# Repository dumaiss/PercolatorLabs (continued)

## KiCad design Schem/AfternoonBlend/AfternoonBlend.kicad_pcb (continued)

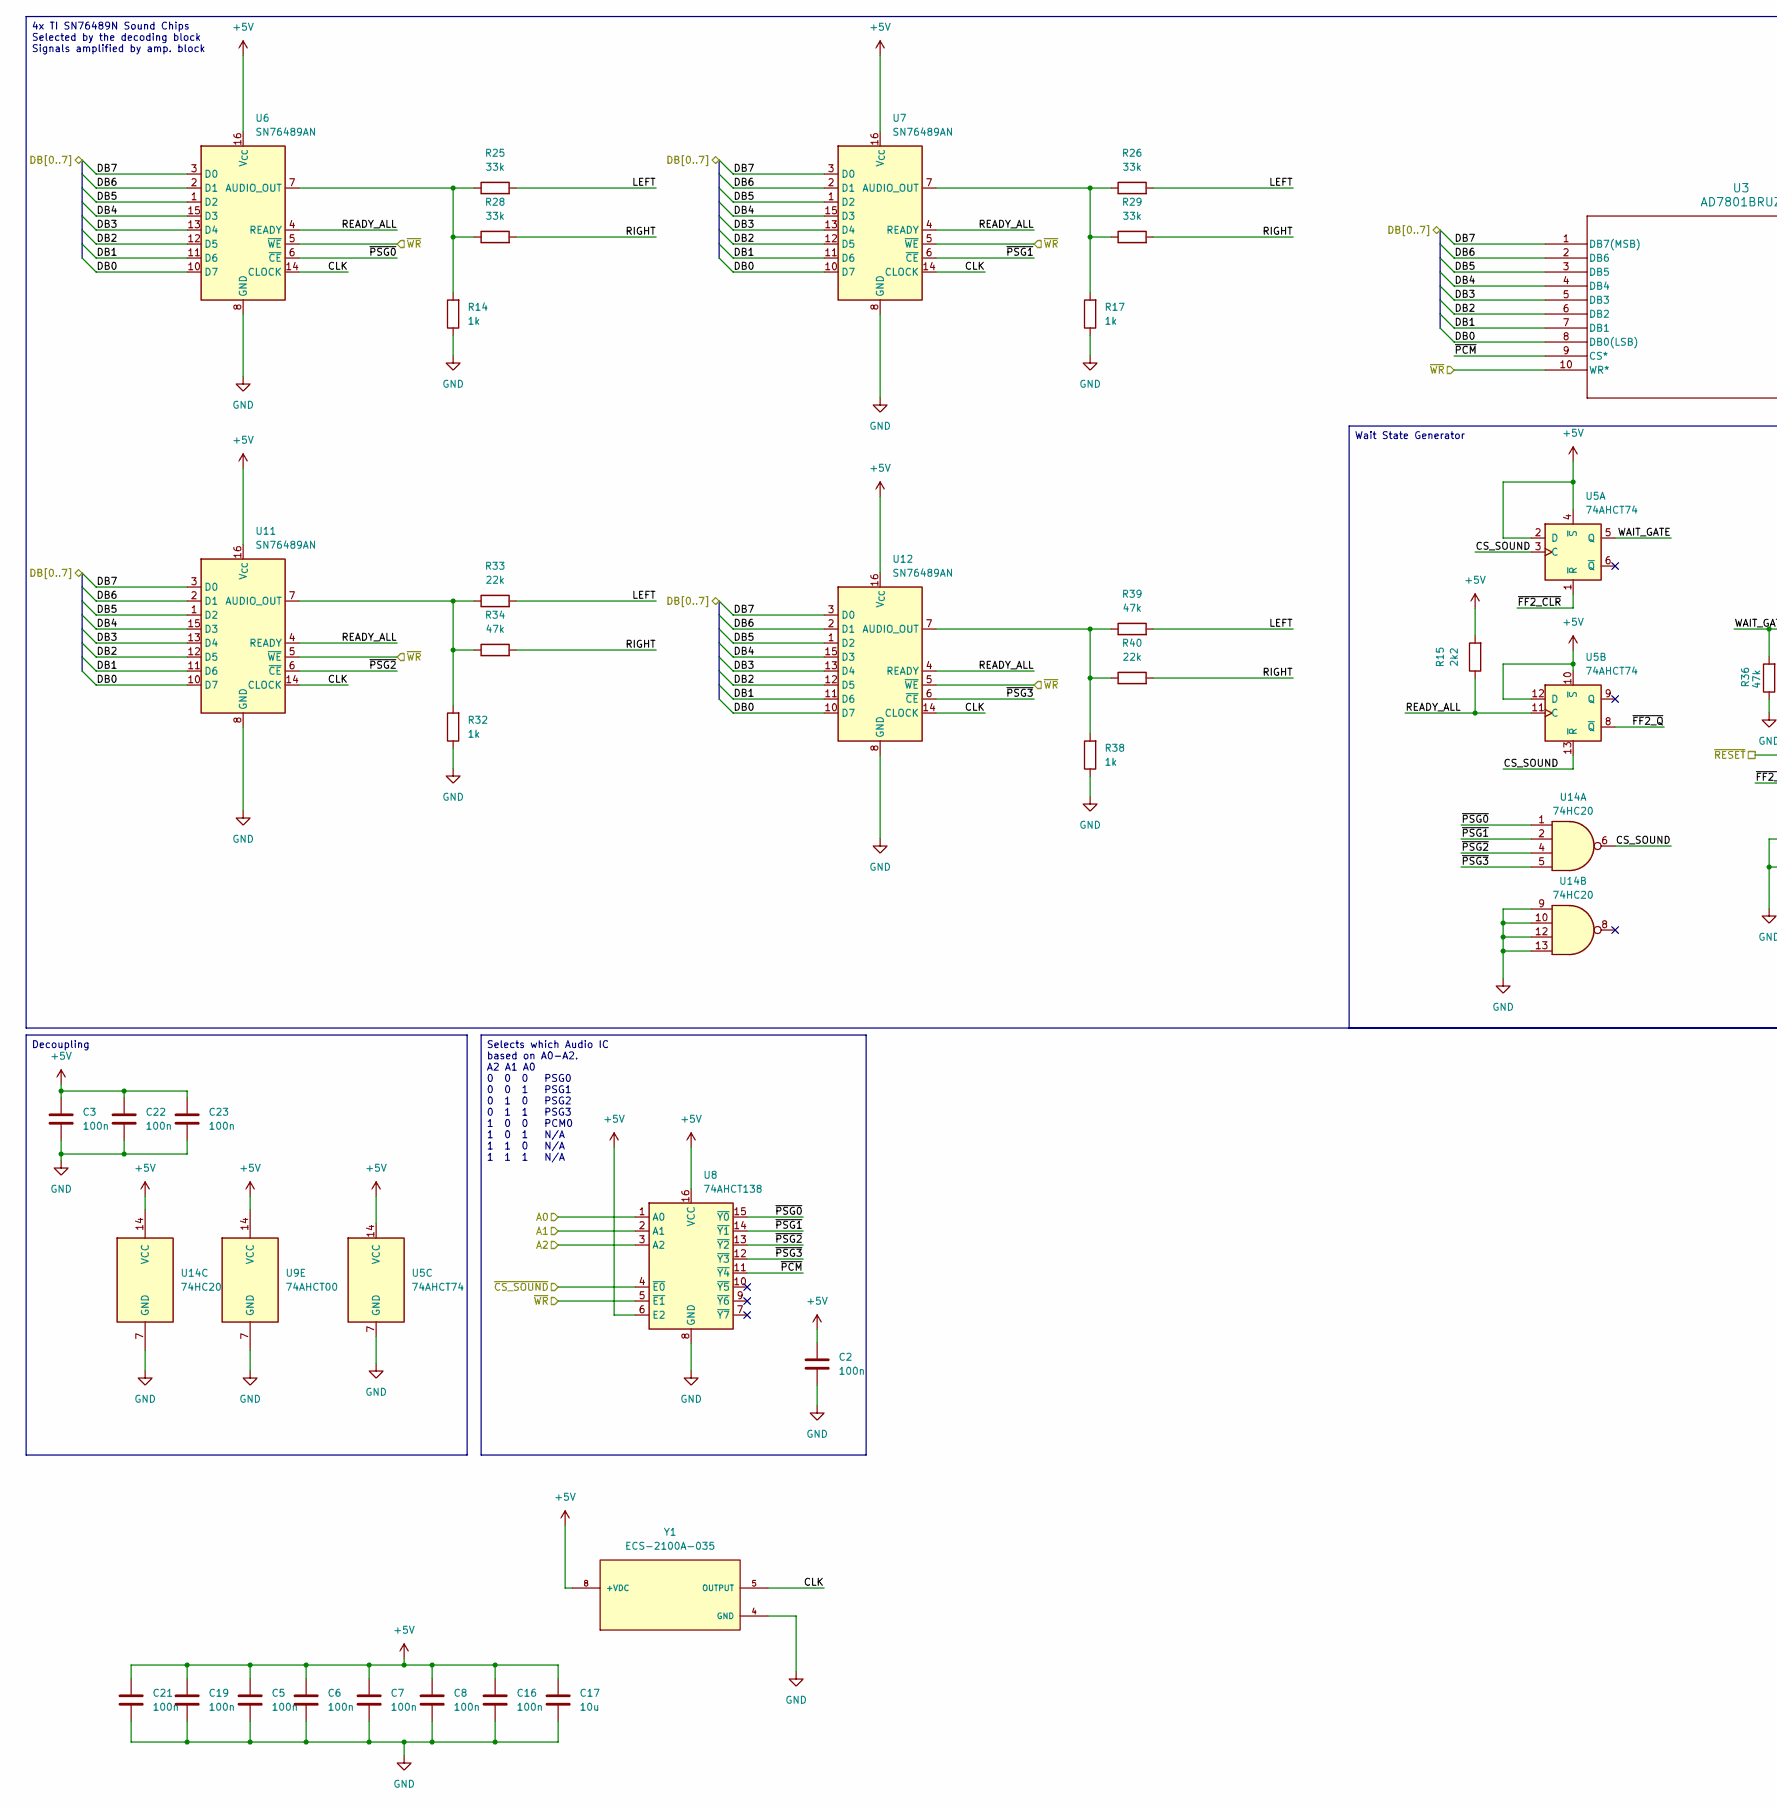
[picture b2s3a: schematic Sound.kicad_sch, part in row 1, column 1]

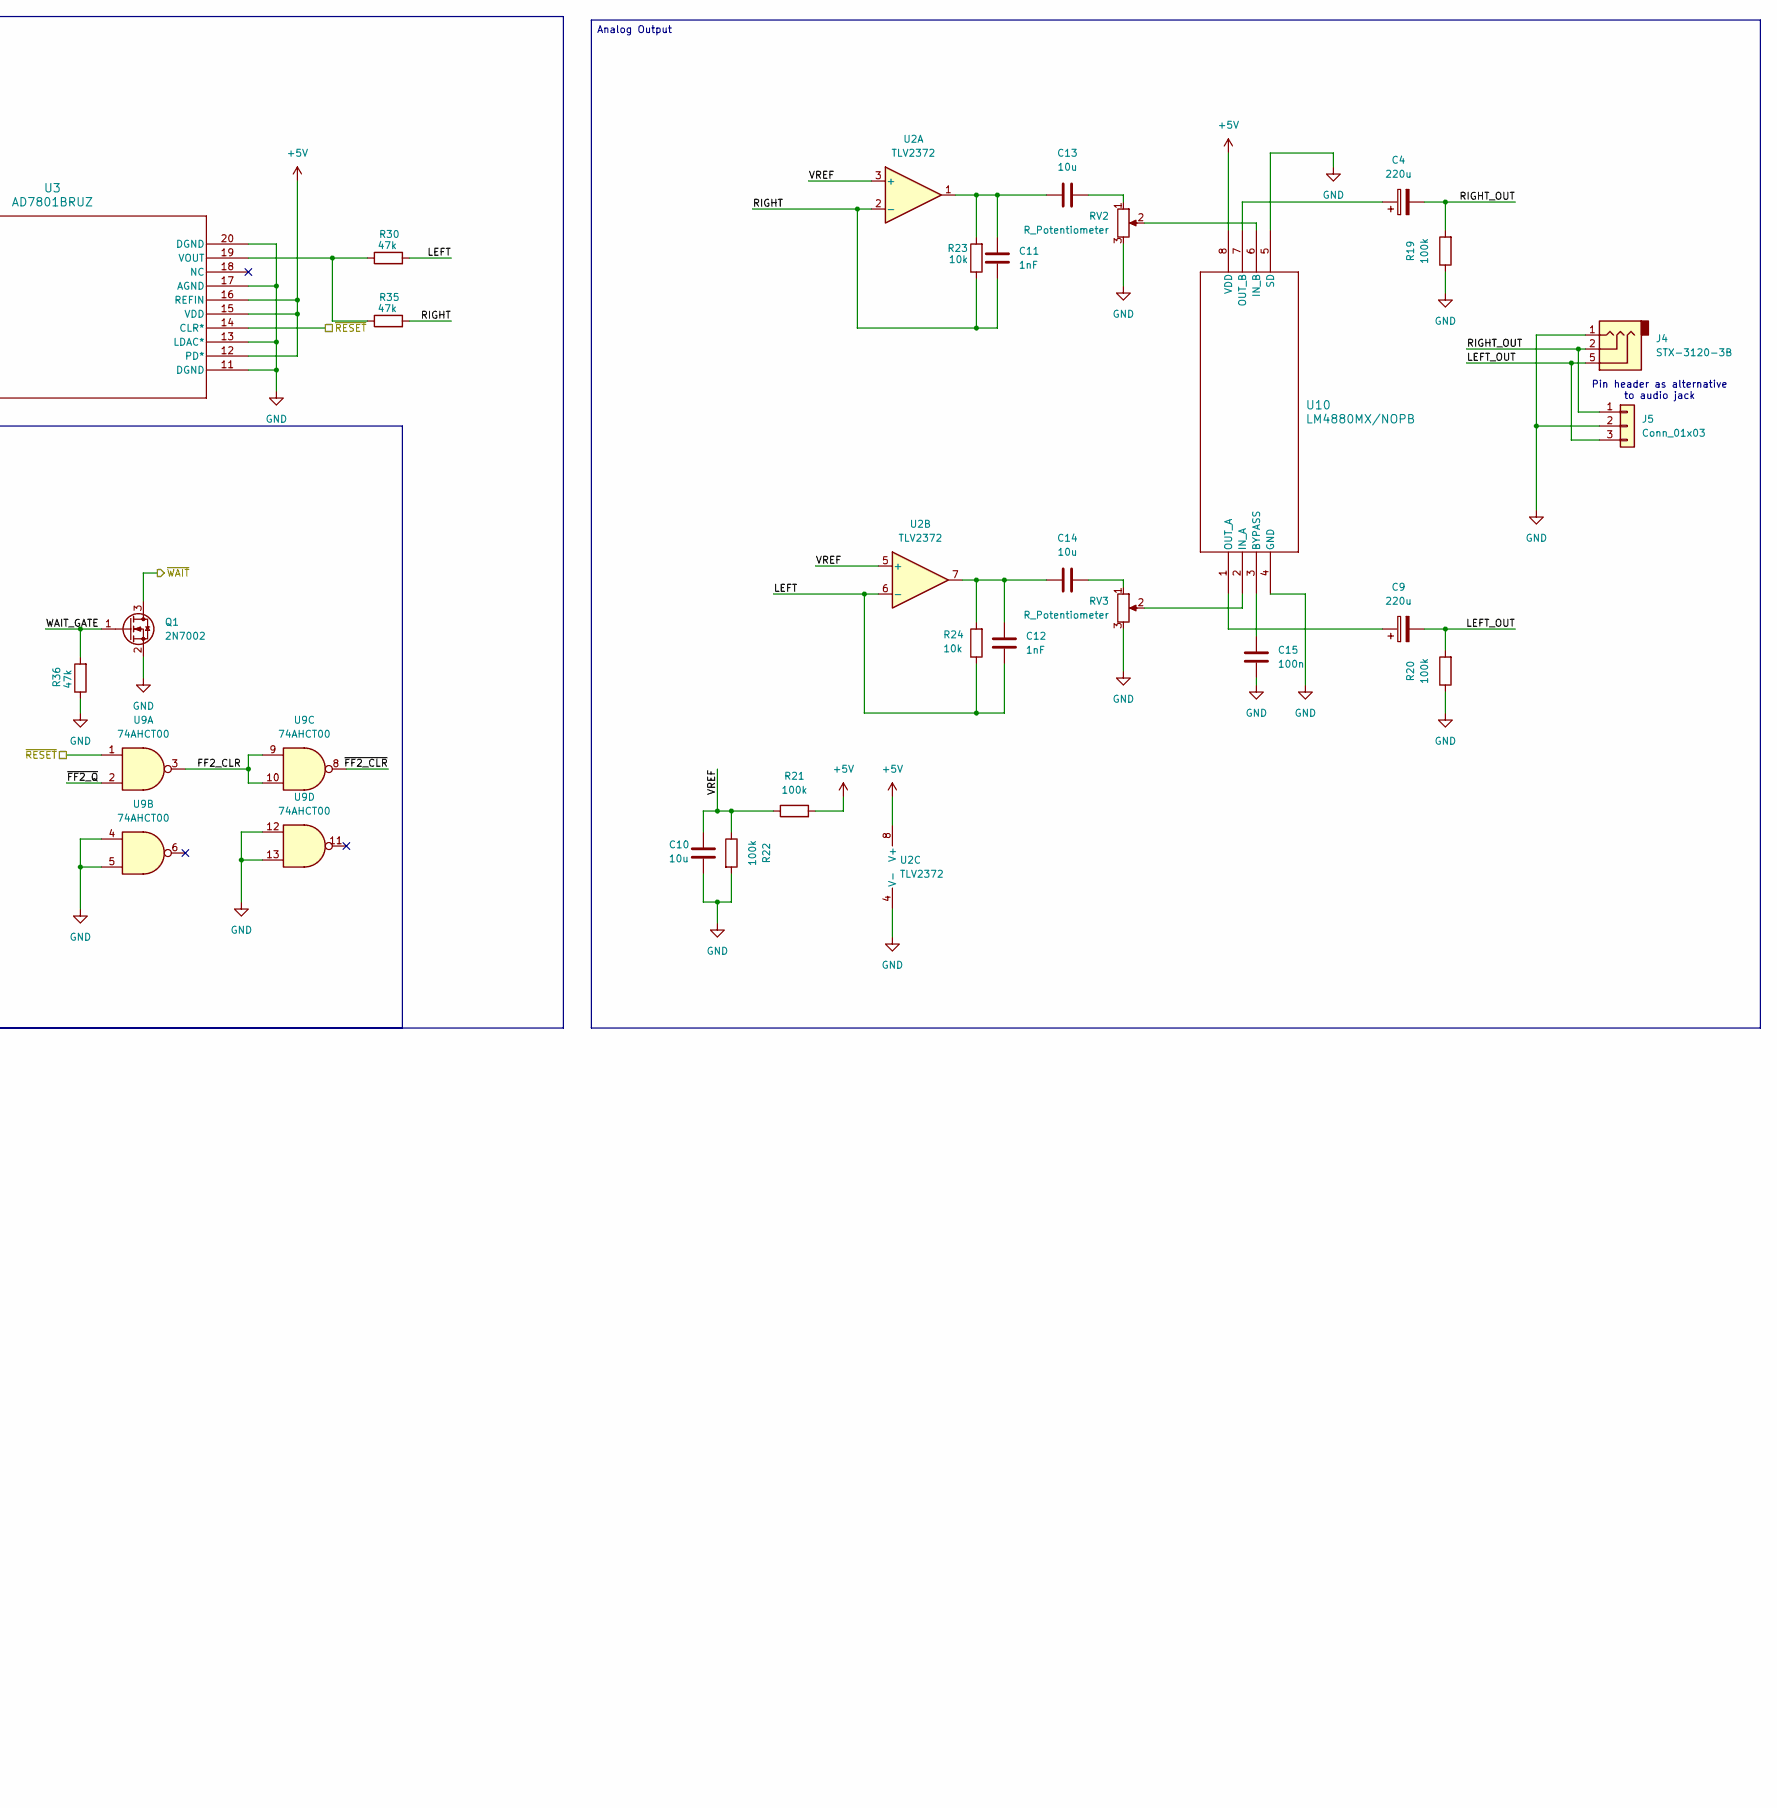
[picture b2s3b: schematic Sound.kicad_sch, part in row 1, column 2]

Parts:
C2, C3, C5, C6, C7, C8, C15, C16, C19, C21, C22, C23: 100n; C_0603_1608Metric; MANUFACTURER_PART_NUMBER C0603C104K5RACTU
C4, C9: 220u; CP_Radial_D6.3mm_P2.50mm; MANUFACTURER_PART_NUMBER 16ZLH220MEFCT16.3X11
C10, C13, C14, C17: 10u; C_0603_1608Metric; MANUFACTURER_PART_NUMBER CL10X106MO8NRNC
C11, C12: 1nF; C_0603_1608Metric; MANUFACTURER_PART_NUMBER C0603C102J5GACTU
J4: STX-3120-3B; KYCON_STX-3120-3B; MANUFACTURER_PART_NUMBER STX-3120-3B
J5: Conn_01x03; PinHeader_1x03_P2.54mm_Vertical; MANUFACTURER_PART_NUMBER 732-5301-ND
Q1: 2N7002; SOT-23; MANUFACTURER_PART_NUMBER BSS138
R14, R17, R32, R38: 1k; R_0603_1608Metric; MANUFACTURER_PART_NUMBER RMCF0603FT1K00
R15: 2k2; R_0603_1608Metric; MANUFACTURER_PART_NUMBER RC0603FR-072K2L
R19, R20, R21, R22: 100k; R_0603_1608Metric; MANUFACTURER_PART_NUMBER RC0603FR-07100KL
R23, R24: 10k; R_0603_1608Metric; MANUFACTURER_PART_NUMBER RC0603FR-0710KL
R25, R26, R28, R29: 33k; R_0603_1608Metric; MANUFACTURER_PART_NUMBER RC0603FR-0733KL
R30, R34, R35, R36, R39: 47k; R_0603_1608Metric; MANUFACTURER_PART_NUMBER RC0603FR-0747KL
R33, R40: 22k; R_0603_1608Metric; MANUFACTURER_PART_NUMBER RC0603FR-0722KL
RV2, RV3: R_Potentiometer; Potentiometer_Bourns_3266W_Vertical; MANUFACTURER_PART_NUMBER 3266W-1-103LF
U2: TLV2372; SOIC-8_3.9x4.9mm_P1.27mm; MANUFACTURER_PART_NUMBER TLV2372IDR
U3: AD7801BRUZ; RU_20_ADI; MANUFACTURER_PART_NUMBER AD7801BRUZ
U5: 74AHCT74; TSSOP-14_4.4x5mm_P0.65mm; MANUFACTURER_PART_NUMBER 74AHCT74PW,118
U6, U7, U11, U12: SN76489AN; DIP-16_W7.62mm_Socket; MANUFACTURER_PART_NUMBER 1-2199298-4
U8: 74AHCT138; SOIC-16_3.9x9.9mm_P1.27mm; MANUFACTURER_PART_NUMBER SN74AHCT138PWR
U9: 74AHCT00; TSSOP-14_4.4x5mm_P0.65mm; MANUFACTURER_PART_NUMBER 74AHCT00PW,118
U10: LM4880MX/NOPB; M08A_TEX; MANUFACTURER_PART_NUMBER LM4880MX/NOPB
U14: 74HC20; TSSOP-14_4.4x5mm_P0.65mm; MANUFACTURER_PART_NUMBER MC74HC20ADTR2G
Y1: ECS-2100A-035; OSC_ECS-2100AX-147.4; PARTREV N/A

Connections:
+5V: C2.1, C3.1, C5.1, C6.1, C7.1, C8.1, C16.1, C17.1, C19.1, C21.1, C22.1, C23.1, R15.2, R21.2, U2.8 (V+), U3.12 (PD*), U3.15 (VDD), U3.16 (REFIN), U5.2 (D), U5.4 (~S), U5.10 (~S), U5.12 (D), U5.14 (VCC), U6.16 (V_{CC}), U7.16 (V_{CC}), U8.6 (E2), U8.16 (VCC), U9.14 (VCC), U10.8 (VDD), U11.16 (V_{CC}), U12.16 (V_{CC}), U14.14 (VCC), Y1.8 (+VDC); also elsewhere on the board
/Device Select Decode/~CS_SOUND: U8.4 (~E0); also elsewhere on the board
/Sound/A0: U8.1 (A0); also elsewhere on the board
/Sound/A1: U8.2 (A1); also elsewhere on the board
/Sound/A2: U8.3 (A2); also elsewhere on the board
/Sound/CLK: U6.14 (CLOCK), U7.14 (CLOCK), U11.14 (CLOCK), U12.14 (CLOCK), Y1.5 (OUTPUT)
/Sound/CS_SOUND: U5.3 (C), U5.13 (~R), U14.6
/Sound/DB0: U3.8 (DB0(LSB)), U6.10 (D7), U7.10 (D7), U11.10 (D7), U12.10 (D7); also elsewhere on the board
/Sound/DB1: U3.7 (DB1), U6.11 (D6), U7.11 (D6), U11.11 (D6), U12.11 (D6); also elsewhere on the board
/Sound/DB2: U3.6 (DB2), U6.12 (D5), U7.12 (D5), U11.12 (D5), U12.12 (D5); also elsewhere on the board
/Sound/DB3: U3.5 (DB3), U6.13 (D4), U7.13 (D4), U11.13 (D4), U12.13 (D4); also elsewhere on the board
/Sound/DB4: U3.4 (DB4), U6.15 (D3), U7.15 (D3), U11.15 (D3), U12.15 (D3); also elsewhere on the board
/Sound/DB5: U3.3 (DB5), U6.1 (D2), U7.1 (D2), U11.1 (D2), U12.1 (D2); also elsewhere on the board
/Sound/DB6: U3.2 (DB6), U6.2 (D1), U7.2 (D1), U11.2 (D1), U12.2 (D1); also elsewhere on the board
/Sound/DB7: U3.1 (DB7(MSB)), U6.3 (D0), U7.3 (D0), U11.3 (D0), U12.3 (D0); also elsewhere on the board
/Sound/FF2_CLR: U9.3, U9.9, U9.10
/Sound/LEFT: C12.1, R24.1, R25.2, R26.2, R30.2, R33.2, R39.2, U2.6 (-)
/Sound/LEFT_OUT: C9.2, J4.5, J5.3, R20.2
/Sound/READY_ALL: R15.1, U5.11 (C), U6.4 (READY), U7.4 (READY), U11.4 (READY), U12.4 (READY)
/Sound/RIGHT: C11.1, R23.1, R28.2, R29.2, R34.2, R35.2, R40.2, U2.2 (-)
/Sound/RIGHT_OUT: C4.2, J4.2, J5.1, R19.2
/Sound/VREF: C10.2, R21.1, R22.1, U2.3 (+), U2.5 (+)
/Sound/WAIT_GATE: Q1.1 (G), R36.2, U5.5 (Q)
/Sound/~FF2_CLR: U5.1 (~R), U9.8
/Sound/~FF2_Q: U5.8 (~Q), U9.2
/Sound/~PCM: U3.9 (CS*), U8.11 (~Y4)
/Sound/~PSG0: U6.6 (~CE), U8.15 (~Y0), U14.1
/Sound/~PSG1: U7.6 (~CE), U8.14 (~Y1), U14.2
/Sound/~PSG2: U8.13 (~Y2), U11.6 (~CE), U14.4
/Sound/~PSG3: U8.12 (~Y3), U12.6 (~CE), U14.5
/Sound/~RESET: U3.14 (CLR*), U9.1; also elsewhere on the board
/Sound/~WAIT: Q1.3 (D); also elsewhere on the board
/Sound/~WR: U3.10 (WR*), U6.5 (~WE), U7.5 (~WE), U8.5 (~E1), U11.5 (~WE), U12.5 (~WE); also elsewhere on the board
GND: C2.2, C3.2, C5.2, C6.2, C7.2, C8.2, C10.1, C15.1, C16.2, C17.2, C19.2, C21.2, C22.2, C23.2, J4.1, J5.2, Q1.2 (S), R14.1, R17.1, R19.1, R20.1, R22.2, R32.1, R36.1, R38.1, RV2.3, RV3.3, U2.4 (V-), U3.11 (DGND), U3.13 (LDAC*), U3.17 (AGND), U3.20 (DGND), U5.7 (GND), U6.8 (GND), U7.8 (GND), U8.8 (GND), U9.4, U9.5, U9.7 (GND), U9.12, U9.13, U10.4 (GND), U10.5 (SD), U11.8 (GND), U12.8 (GND), U14.7 (GND), U14.9, U14.10, U14.12, U14.13, Y1.4 (GND); also elsewhere on the board
unnamed: C11.2, C13.1, R23.2, U2.1
unnamed: C12.2, C14.1, R24.2, U2.7
unnamed: C13.2, RV2.1
unnamed: C14.2, RV3.1
unnamed: R30.1, R35.1, U3.19 (VOUT)
unnamed: R14.2, R25.1, R28.1, U6.7 (AUDIO_OUT)
unnamed: R17.2, R26.1, R29.1, U7.7 (AUDIO_OUT)
unnamed: C15.2, U10.3 (BYPASS)
unnamed: RV3.2, U10.2 (IN_A)
unnamed: RV2.2, U10.6 (IN_B)
unnamed: C9.1, U10.1 (OUT_A)
unnamed: C4.1, U10.7 (OUT_B)
unnamed: R32.2, R33.1, R34.1, U11.7 (AUDIO_OUT)
unnamed: R38.2, R39.1, R40.1, U12.7 (AUDIO_OUT)

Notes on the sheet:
Pin header as alternative to audio jack
Wait State Generator
Decoupling
Analog Output
Selects which Audio IC based on A0-A2. A2 A1 A0 0 0 0 PSG0 0 0 1 PSG1 0 1 0 PSG2 0 1 1 PSG3 1 0 0 PCM0 1 0 1 N/A 1 1 0 N/A 1 1 1 N/A
4x TI SN76489N Sound Chips Selected by the decoding block Signals amplified by amp. block

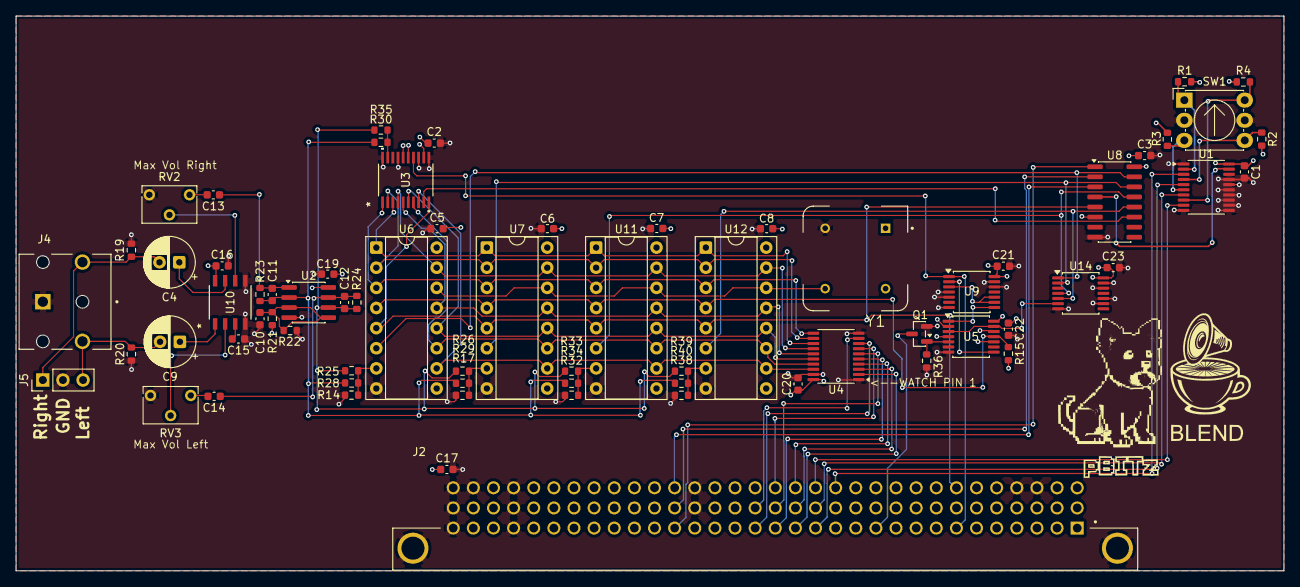
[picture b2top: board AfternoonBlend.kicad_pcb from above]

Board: 4 copper layers, 160.0 x 70.0 mm, 69 parts (0 on the bottom side), 64 nets.

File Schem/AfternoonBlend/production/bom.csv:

Designator,Footprint,Quantity,Value,LCSC Part #
"C1, C15, C16, C19, C2, C20, C21, C22, C23, C3, C5, C6, C7, C8",0603,14,100n,
"C10, C13, C14, C17",0603,4,10u,
"C11, C12",0603,2,1nF,
"C4, C9",CP_Radial_D6.3mm_P2.50mm,2,220u,
J2,AMPHENOL_86093967113T55F1LF,1,~,
J4,KYCON_STX-3120-3B,1,STX-3120-3B,
J5,PinHeader_1x03_P2.54mm_Vertical,1,Conn_01x03,
Q1,SOT-23,1,2N7002,
"R1, R2, R3, R4",0603,4,4k7,
"R14, R17, R32, R38",0603,4,1k,
R15,0603,1,2k2,
"R19, R20, R21, R22",0603,4,100k,
"R23, R24",0603,2,10k,
"R25, R26, R28, R29",0603,4,33k,
"R30, R34, R35, R36, R39",0603,5,47k,
"R33, R40",0603,2,22k,
"RV2, RV3",Potentiometer_Bourns_3266W_Vertical,2,R_Potentiometer,
SW1,Nidec_Copal_SH-7010C,1,SW_Coded_SH-7070,
U1,TSSOP-20_4.4x6.5mm_P0.65mm,1,74HC688,
U10,M08A_TEX,1,LM4880MX/NOPB,
"U11, U12, U6, U7",DIP-16_W7.62mm_Socket,4,SN76489AN,
U14,TSSOP-14_4.4x5mm_P0.65mm,1,74HC20,
U2,SOIC-8_3.9x4.9mm_P1.27mm,1,TLV2372,
U3,RU_20_ADI,1,AD7801BRUZ,
U4,TSSOP-20_4.4x6.5mm_P0.65mm,1,74HCT541,
U5,TSSOP-14_4.4x5mm_P0.65mm,1,74AHCT74,
U8,SOIC-16_3.9x9.9mm_P1.27mm,1,74AHCT138,
U9,TSSOP-14_4.4x5mm_P0.65mm,1,74AHCT00,
Y1,OSC_ECS-2100AX-147.4,1,ECS-2100A-035,

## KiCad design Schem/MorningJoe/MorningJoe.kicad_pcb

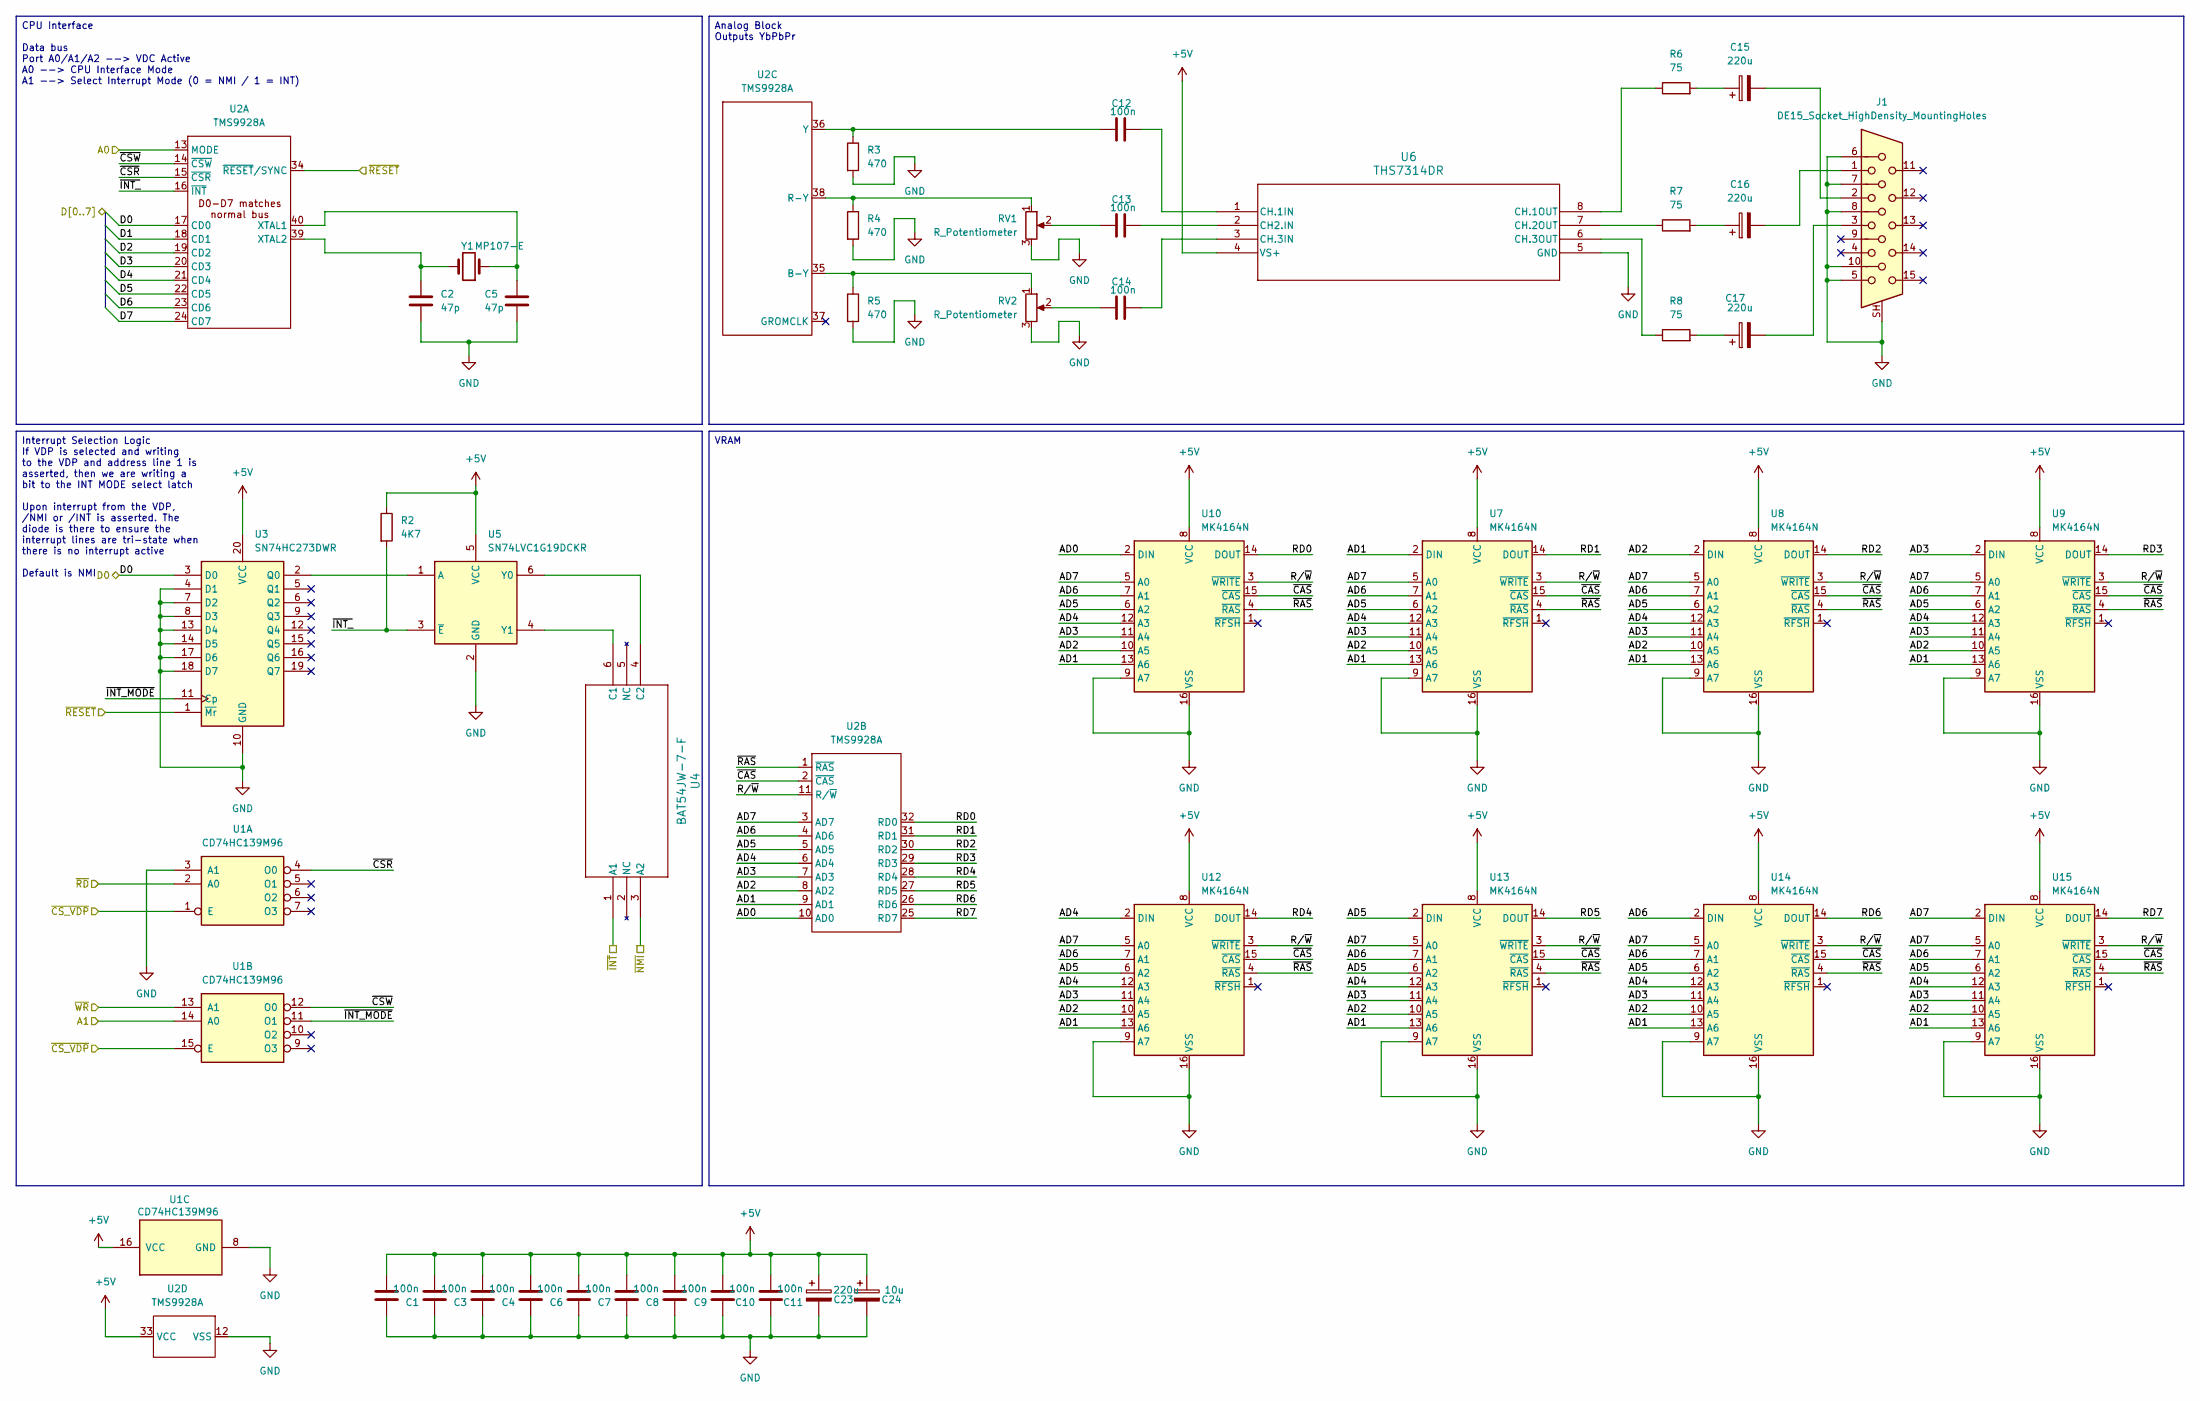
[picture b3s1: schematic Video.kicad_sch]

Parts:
C1, C3, C4, C6, C7, C8, C9, C10, C11, C12, C13, C14: 100n; C_0603_1608Metric; MANUFACTURER_PART_NUMBER C0603C104K5RACTU
C2, C5: 47p; C_0603_1608Metric; MANUFACTURER_PART_NUMBER 885012006021
C15, C16, C17, C23: 220u; CP_Radial_D6.3mm_P2.50mm; MANUFACTURER_PART_NUMBER 16ZLH220MEFCT16.3X11
C24: 10u; CP_Radial_D5.0mm_P2.00mm; MANUFACTURER_PART_NUMBER EEA-GA1E100H
J1: DE15_Socket_HighDensity_MountingHoles; DSUB-15-HD_Socket_Horizontal_P2.29x2.54mm_EdgePinOffset8.35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; MANUFACTURER_PART_NUMBER L77HDE15SD1CH4FVGA
R2: 4K7; R_0603_1608Metric; MANUFACTURER_PART_NUMBER CRCW06034K70FKEA
R3, R4, R5: 470; R_0603_1608Metric; MANUFACTURER_PART_NUMBER RC0603JR-07470RL
R6, R7, R8: 75; R_0603_1608Metric; MANUFACTURER_PART_NUMBER RC0603FR-0775RL
RV1, RV2: R_Potentiometer; Potentiometer_Bourns_3266W_Vertical; MANUFACTURER_PART_NUMBER 3266W-1-103LF
U1: CD74HC139M96; SOIC-16_3.9x9.9mm_P1.27mm; MANUFACTURER_PART_NUMBER CD74HC139M96
U2: TMS9928A; DIP-40_W15.24mm_Socket; MANUFACTURER_PART_NUMBER A 40-LC-TT
U3: SN74HC273DWR; SOIC-20W_7.5x12.8mm_P1.27mm; MANUFACTURER_PART_NUMBER SN74HC273DWR
U4: BAT54JW-7-F; SOT-363_SC-70-6; MANUFACTURER_PART_NUMBER BAT54JW-7-F
U5: SN74LVC1G19DCKR; SOT-363_SC-70-6; MANUFACTURER_PART_NUMBER SN74LVC1G19DCKR
U6: THS7314DR; D8; MANUFACTURER_PART_NUMBER THS7314DR
U7, U8, U9, U10, U12, U13, U14, U15: MK4164N; DIP-16_W7.62mm_Socket; MANUFACTURER_PART_NUMBER 1-2199298-4
Y1: MP107-E; Crystal_HC49-U_Vertical; MANUFACTURER_PART_NUMBER MP107-E

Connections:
+5V: C1.1, C3.1, C4.1, C6.1, C7.1, C8.1, C9.1, C10.1, C11.1, C23.1, C24.1, R2.1, U1.16 (VCC), U2.33 (VCC), U3.20 (VCC), U5.5 (VCC), U6.4 (VS+), U7.8 (VCC), U8.8 (VCC), U9.8 (VCC), U10.8 (VCC), U12.8 (VCC), U13.8 (VCC), U14.8 (VCC), U15.8 (VCC); also elsewhere on the board
/Device Select Decode/~CS_VDP: U1.1 (E), U1.15 (E); also elsewhere on the board
/Video/A0: U2.13 (MODE); also elsewhere on the board
/Video/A1: U1.14 (A0); also elsewhere on the board
/Video/AD0: U2.10 (AD0), U10.2 (DIN)
/Video/AD1: U2.9 (AD1), U7.2 (DIN), U7.13 (A6), U8.13 (A6), U9.13 (A6), U10.13 (A6), U12.13 (A6), U13.13 (A6), U14.13 (A6), U15.13 (A6)
/Video/AD2: U2.8 (AD2), U7.10 (A5), U8.2 (DIN), U8.10 (A5), U9.10 (A5), U10.10 (A5), U12.10 (A5), U13.10 (A5), U14.10 (A5), U15.10 (A5)
/Video/AD3: U2.7 (AD3), U7.11 (A4), U8.11 (A4), U9.2 (DIN), U9.11 (A4), U10.11 (A4), U12.11 (A4), U13.11 (A4), U14.11 (A4), U15.11 (A4)
/Video/AD4: U2.6 (AD4), U7.12 (A3), U8.12 (A3), U9.12 (A3), U10.12 (A3), U12.2 (DIN), U12.12 (A3), U13.12 (A3), U14.12 (A3), U15.12 (A3)
/Video/AD5: U2.5 (AD5), U7.6 (A2), U8.6 (A2), U9.6 (A2), U10.6 (A2), U12.6 (A2), U13.2 (DIN), U13.6 (A2), U14.6 (A2), U15.6 (A2)
/Video/AD6: U2.4 (AD6), U7.7 (A1), U8.7 (A1), U9.7 (A1), U10.7 (A1), U12.7 (A1), U13.7 (A1), U14.2 (DIN), U14.7 (A1), U15.7 (A1)
/Video/AD7: U2.3 (AD7), U7.5 (A0), U8.5 (A0), U9.5 (A0), U10.5 (A0), U12.5 (A0), U13.5 (A0), U14.5 (A0), U15.2 (DIN), U15.5 (A0)
/Video/D0: U2.17 (CD0), U3.3 (D0); also elsewhere on the board
/Video/D1: U2.18 (CD1); also elsewhere on the board
/Video/D2: U2.19 (CD2); also elsewhere on the board
/Video/D3: U2.20 (CD3); also elsewhere on the board
/Video/D4: U2.21 (CD4); also elsewhere on the board
/Video/D5: U2.22 (CD5); also elsewhere on the board
/Video/D6: U2.23 (CD6); also elsewhere on the board
/Video/D7: U2.24 (CD7); also elsewhere on the board
/Video/RD0: U2.32 (RD0), U10.14 (DOUT)
/Video/RD1: U2.31 (RD1), U7.14 (DOUT)
/Video/RD2: U2.30 (RD2), U8.14 (DOUT)
/Video/RD3: U2.29 (RD3), U9.14 (DOUT)
/Video/RD4: U2.28 (RD4), U12.14 (DOUT)
/Video/RD5: U2.27 (RD5), U13.14 (DOUT)
/Video/RD6: U2.26 (RD6), U14.14 (DOUT)
/Video/RD7: U2.25 (RD7), U15.14 (DOUT)
/Video/R/~W: U2.11 (R/~W), U7.3 (~WRITE), U8.3 (~WRITE), U9.3 (~WRITE), U10.3 (~WRITE), U12.3 (~WRITE), U13.3 (~WRITE), U14.3 (~WRITE), U15.3 (~WRITE)
/Video/~CAS: U2.2 (~CAS), U7.15 (~CAS), U8.15 (~CAS), U9.15 (~CAS), U10.15 (~CAS), U12.15 (~CAS), U13.15 (~CAS), U14.15 (~CAS), U15.15 (~CAS)
/Video/~CSR: U1.4 (O0), U2.15 (~CSR)
/Video/~CSW: U1.12 (O0), U2.14 (~CSW)
/Video/~INT_MODE: U1.11 (O1), U3.11 (Cp)
/Video/~INT_: R2.2, U2.16 (~INT), U5.3 (~E)
/Video/~INT: U4.1 (A1); also elsewhere on the board
/Video/~NMI: U4.3 (A2); also elsewhere on the board
/Video/~RAS: U2.1 (~RAS), U7.4 (~RAS), U8.4 (~RAS), U9.4 (~RAS), U10.4 (~RAS), U12.4 (~RAS), U13.4 (~RAS), U14.4 (~RAS), U15.4 (~RAS)
/Video/~RD: U1.2 (A0); also elsewhere on the board
/Video/~RESET: U2.34 (~RESET/SYNC), U3.1 (~Mr); also elsewhere on the board
/Video/~WR: U1.13 (A1); also elsewhere on the board
GND: C1.2, C2.1, C3.2, C4.2, C5.1, C6.2, C7.2, C8.2, C9.2, C10.2, C11.2, C23.2, C24.2, J1.5, J1.6, J1.7, J1.8, J1.10, J1.SH, R3.2, R4.2, R5.2, RV1.3, RV2.3, U1.3 (A1), U1.8 (GND), U2.12 (VSS), U3.4 (D1), U3.7 (D2), U3.8 (D3), U3.10 (GND), U3.13 (D4), U3.14 (D5), U3.17 (D6), U3.18 (D7), U5.2 (GND), U6.5 (GND), U7.9 (A7), U7.16 (VSS), U8.9 (A7), U8.16 (VSS), U9.9 (A7), U9.16 (VSS), U10.9 (A7), U10.16 (VSS), U12.9 (A7), U12.16 (VSS), U13.9 (A7), U13.16 (VSS), U14.9 (A7), U14.16 (VSS), U15.9 (A7), U15.16 (VSS); also elsewhere on the board
unnamed: C13.1, RV1.2
unnamed: C14.1, RV2.2
unnamed: C15.1, R6.2
unnamed: C15.2, J1.2
unnamed: C16.1, R7.2
unnamed: C16.2, J1.1
unnamed: C17.1, R8.2
unnamed: C17.2, J1.3
unnamed: C5.2, U2.40 (XTAL1), Y1.1
unnamed: C2.2, U2.39 (XTAL2), Y1.2
unnamed: R5.1, RV2.1, U2.35 (B-Y)
unnamed: R4.1, RV1.1, U2.38 (R-Y)
unnamed: C12.1, R3.1, U2.36 (Y)
unnamed: U3.2 (Q0), U5.1 (A)
unnamed: U4.6 (C1), U5.4 (Y1)
unnamed: U4.4 (C2), U5.6 (Y0)
unnamed: C13.2, U6.2 (CH2.IN)
unnamed: C12.2, U6.1 (CH.1IN)
unnamed: R6.1, U6.8 (CH.1OUT)
unnamed: R7.1, U6.7 (CH.2OUT)
unnamed: C14.2, U6.3 (CH.3IN)
unnamed: R8.1, U6.6 (CH.3OUT)

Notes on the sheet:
VRAM
Analog Block Outputs YbPbPr
Interrupt Selection Logic If VDP is selected and writing to the VDP and address line 1 is asserted, then we are writing a bit to the INT MODE select latch Upon interrupt from the VDP, /NMI or /INT is asserted. The diode is there to ensure the interrupt lines are tri-state when there is no interrupt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
CPU Interface Data bus Port A0/A1/A2 --> VDC Active A0 --> CPU Interface Mode A1 --> Select Interrupt Mode (0 = NMI / 1 = INT)

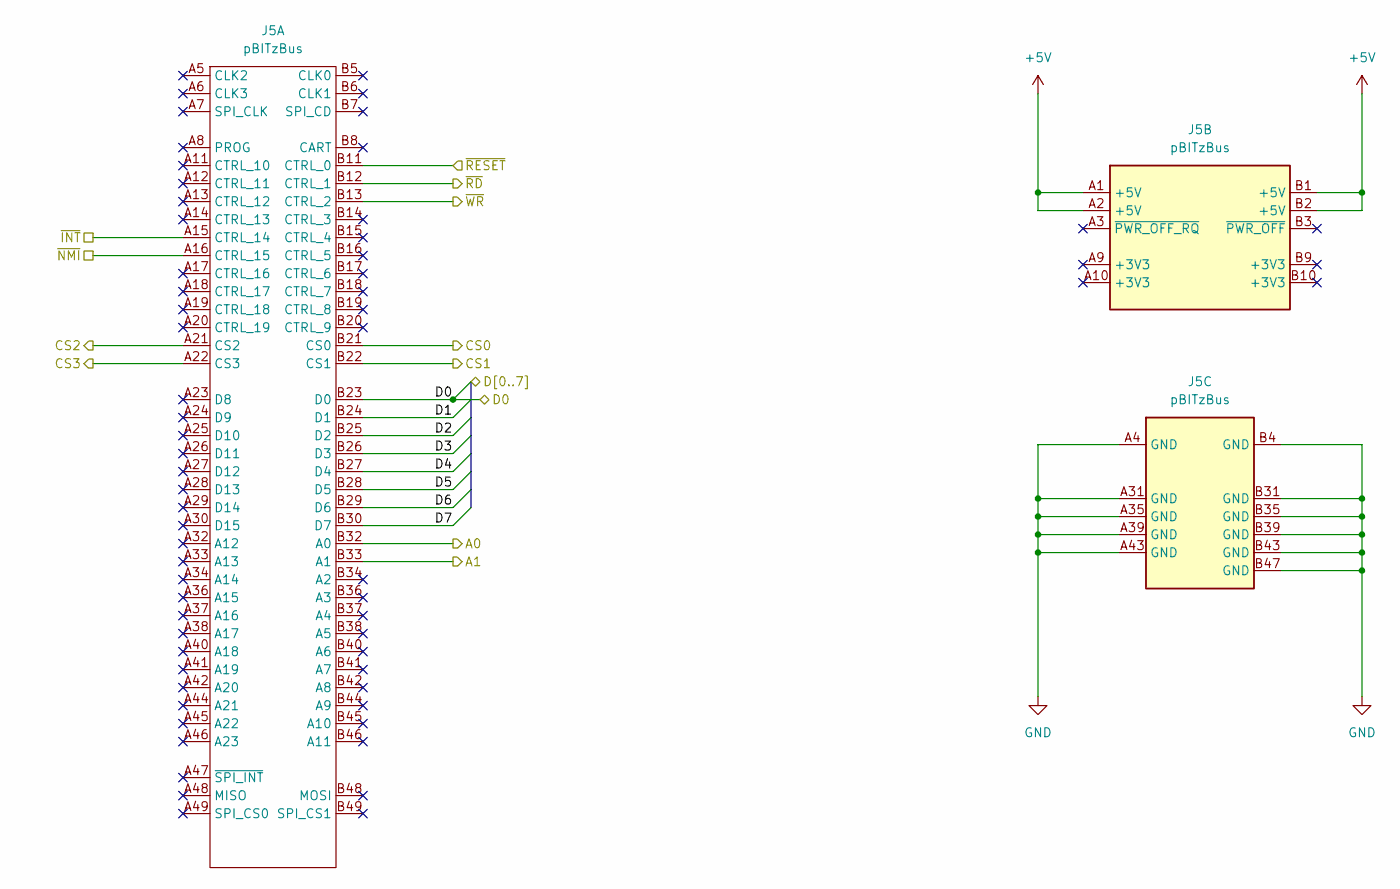
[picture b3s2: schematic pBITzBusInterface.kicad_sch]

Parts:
J5: pBITzBus; BUS_PCIexpress_x8

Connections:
+5V: J5.A1 (+5V), J5.A2 (+5V), J5.B1 (+5V), J5.B2 (+5V); also elsewhere on the board
/Device Select Decode/CS0: J5.B21 (CS0); also elsewhere on the board
/Device Select Decode/CS1: J5.B22 (CS1); also elsewhere on the board
/Device Select Decode/CS2: J5.A21 (CS2); also elsewhere on the board
/Device Select Decode/CS3: J5.A22 (CS3); also elsewhere on the board
/Video/A0: J5.B32 (A0); also elsewhere on the board
/Video/A1: J5.B33 (A1); also elsewhere on the board
/Video/D0: J5.B23 (D0); also elsewhere on the board
/Video/D1: J5.B24 (D1); also elsewhere on the board
/Video/D2: J5.B25 (D2); also elsewhere on the board
/Video/D3: J5.B26 (D3); also elsewhere on the board
/Video/D4: J5.B27 (D4); also elsewhere on the board
/Video/D5: J5.B28 (D5); also elsewhere on the board
/Video/D6: J5.B29 (D6); also elsewhere on the board
/Video/D7: J5.B30 (D7); also elsewhere on the board
/Video/~INT: J5.A15 (CTRL_14); also elsewhere on the board
/Video/~NMI: J5.A16 (CTRL_15); also elsewhere on the board
/Video/~RD: J5.B12 (CTRL_1); also elsewhere on the board
/Video/~RESET: J5.B11 (CTRL_0); also elsewhere on the board
/Video/~WR: J5.B13 (CTRL_2); also elsewhere on the board
GND: J5.A4 (GND), J5.A31 (GND), J5.A35 (GND), J5.A39 (GND), J5.A43 (GND), J5.B4 (GND), J5.B31 (GND), J5.B35 (GND), J5.B39 (GND), J5.B43 (GND), J5.B47 (GND); also elsewhere on the board

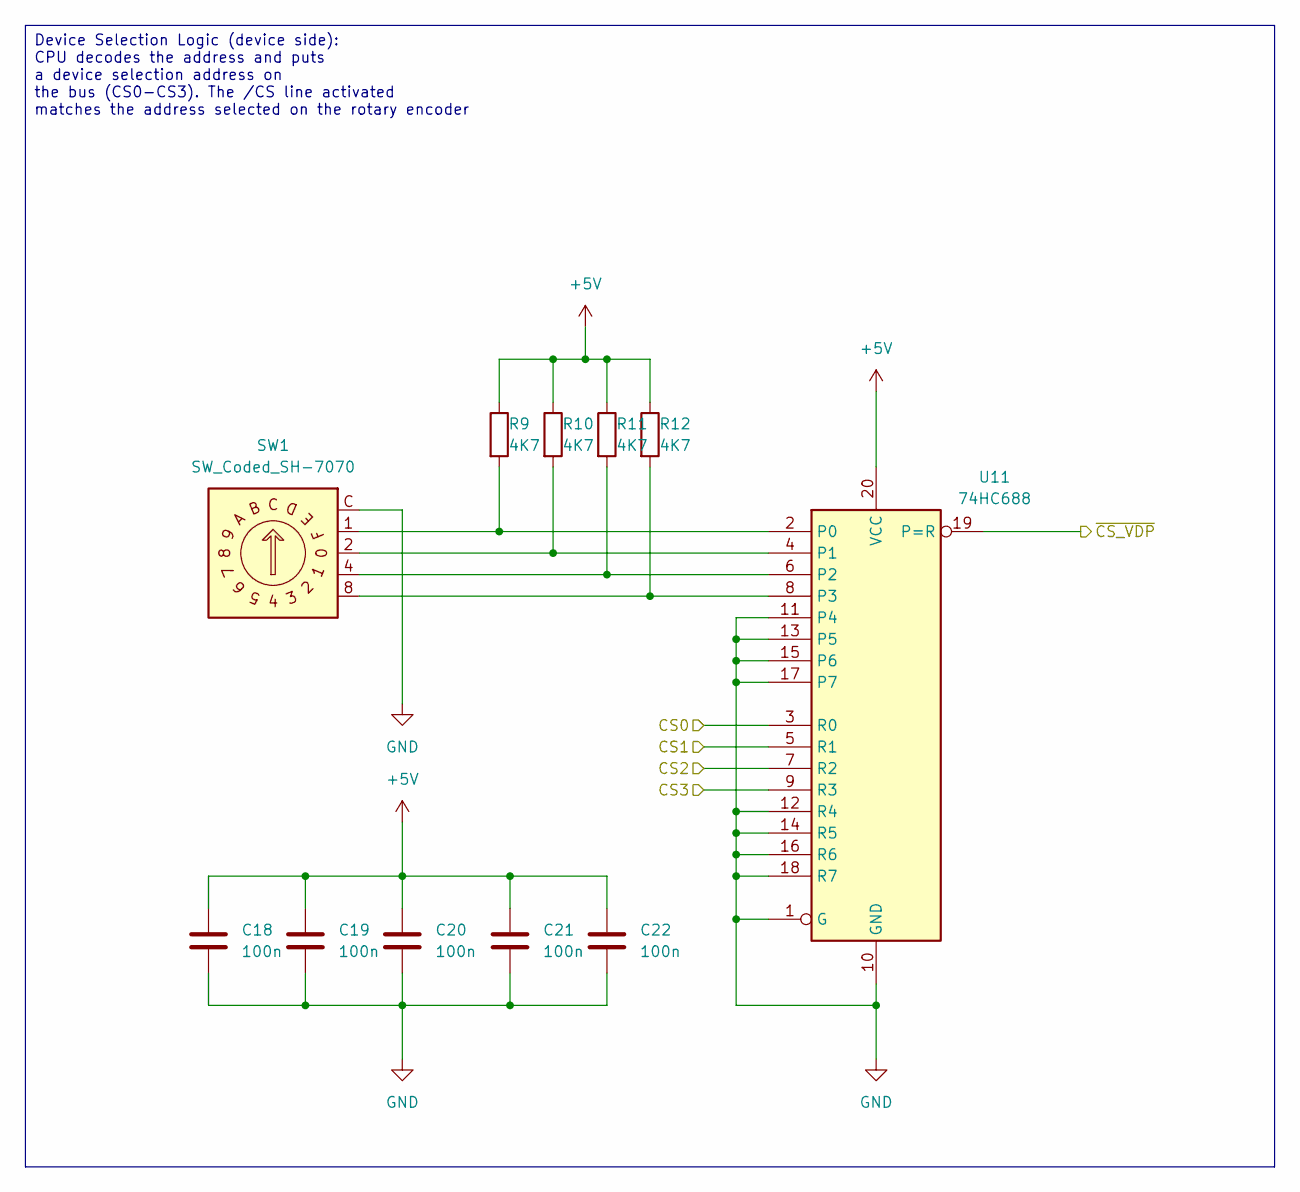
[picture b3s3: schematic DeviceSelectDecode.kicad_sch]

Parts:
C18, C19, C20, C21, C22: 100n; C_0603_1608Metric; MANUFACTURER_PART_NUMBER C0603C104K5RACTU
R9, R10, R11, R12: 4K7; R_0603_1608Metric; MANUFACTURER_PART_NUMBER CRCW06034K70FKEA
SW1: SW_Coded_SH-7070; Nidec_Copal_SH-7010C; MANUFACTURER_PART_NUMBER SH-7070MC
U11: 74HC688; TSSOP-20_4.4x6.5mm_P0.65mm; MANUFACTURER_PART_NUMBER SN74HC688PWR

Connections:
+5V: C18.1, C19.1, C20.1, C21.1, C22.1, R9.1, R10.1, R11.1, R12.1, U11.20 (VCC); also elsewhere on the board
/Device Select Decode/CS0: U11.3 (R0); also elsewhere on the board
/Device Select Decode/CS1: U11.5 (R1); also elsewhere on the board
/Device Select Decode/CS2: U11.7 (R2); also elsewhere on the board
/Device Select Decode/CS3: U11.9 (R3); also elsewhere on the board
/Device Select Decode/~CS_VDP: U11.19 (P=R); also elsewhere on the board
GND: C18.2, C19.2, C20.2, C21.2, C22.2, SW1.C, U11.1 (G), U11.10 (GND), U11.11 (P4), U11.12 (R4), U11.13 (P5), U11.14 (R5), U11.15 (P6), U11.16 (R6), U11.17 (P7), U11.18 (R7); also elsewhere on the board
unnamed: R9.2, SW1.1, U11.2 (P0)
unnamed: R10.2, SW1.2, U11.4 (P1)
unnamed: R11.2, SW1.4, U11.6 (P2)
unnamed: R12.2, SW1.8, U11.8 (P3)

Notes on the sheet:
Device Selection Logic (device side): CPU decodes the address and puts a device selection address on the bus (CS0-CS3). The /CS line activated matches the address selected on the rotary encoder
